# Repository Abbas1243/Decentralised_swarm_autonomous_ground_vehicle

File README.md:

# BE CAPSTONE PROJECT 

## 🤖 Decentralized Swarm Autonomous Ground Vehicles
<p align="left">
  
</p>

---
## 👥 Team Details

| **Sr. No.** | **Name of Student** | **Roll No.** | **Branch** | **Email ID** |
|:---:|:---|:---:|:---|:---|
| 1 | Abbas Najam | 59 |Automation and Robotics | [2023.abbas.najam@ves.ac.in](mailto:2023.abbas.najam@ves.ac.in) |
| 2 | Mayuresh Joshi | 49 | Automation and Robotics | [2023.mayuresh.joshi@ves.ac.in](mailto:2023.mayuresh.joshi@ves.ac.in) |
| 3 | Shravan Umrale | 66 | Automation and Robotics | [2023.shravan.umrale@ves.ac.in](mailto:2023.shravan.umrale@ves.ac.in) |
| 4 | Yash Vaychal | 31 | Automation and Robotics | [2023.yash.vaychal@ves.ac.in](mailto:2023.yash.vaychal@ves.ac.in) |

---

## Guide Details

**Project Guide:**  Deepti Khimani

**Department:** Automation and Robotics  

**Institute:** VESIT, Mumbai

# 📌 Project Overview

Swarm robotics is inspired by the collective behavior observed in nature, such as ants, bees and birds. Many simple units working together can cover more ground, and tolerate the loss of individual units better, than a single capable unit.

This project focuses on the design and development of a **six-robot low-cost differential-drive robotic swarm for cooperative indoor exploration and mapping**.

Each robot is designed around an ESP32-WROOM-32E microcontroller mounted on a custom-designed PCB. The PCB integrates the motor driver and DC-DC buck converter, reducing the need for separate electronic modules and simplifying the overall hardware assembly.

Each robot is equipped with:
- Six VL53L0X Time-of-Flight (ToF) distance sensors.
- One MPU6050 six-axis IMU.
- Two N20 geared DC motors with integrated wheel encoders.
- Two 34 mm rubber drive wheels.
- One ball caster.
- One 7.4 V, 2600 mAh LiPo battery.

The mechanical structure consists of a 3 mm laser-cut MDF base plate, custom 3D-printed PLA motor holders, a caster holder and spacers. M3 nuts and bolts are used for mechanical assembly.

The current implementation assumes that the robots begin from predefined and known starting positions and orientations. Estimating unknown starting poses and automatically aligning independently initialized robot maps are considered future extensions.

### Key Capabilities
Key Capabilities
* 🤖 Low-cost differential-drive robots (ESP32 on custom PCB)
* 📏 6-beam ToF sensing per robot
* 🧭 Odometry from wheel encoders fused with IMU gyro
* 🗺️ Per-robot SLAM using pose graph and scan matching
* 🧩 Merging of all robots' observations into one map
* 📡 Wi-Fi telemetry to a laptop and robot-to-robot pose sharing
* 🚧 Reactive obstacle avoidance and wall following
* 🧠 Decentralized exploration behaviour
* 📊 Live map viewer and replayable data logs
* 📐 Evaluation against tape-measured ground truth
---

# 🎯 Problem Statement

Teams of mobile robots map unknown indoor spaces faster than a single robot, and can keep working if one unit fails. But published multi-robot mapping systems depend on dense 2D LiDAR and a single-board Linux computer on every robot, which puts them out of reach of teaching laboratories and of applications where robots are expendable.

This project therefore designs, builds and evaluates a team of low-cost differential-drive robots, each with only an ESP32, six single-zone ToF sensors, an IMU and wheel encoders, that explore a known-size indoor arena from **known starting poses**, while a laptop combines their data into one two-dimensional map. The problem includes determining, **by measurement and not by assumption**, how accurate such a map is and which sensing, odometry and algorithmic factors limit that accuracy.

---

# 🚀 Objectives

The major objectives of this project are:

* Develop a decentralized multi-robot swarm system.
* Enable communication between multiple autonomous ground vehicles.
* Implement autonomous navigation.
* Implement mapping and localization.
* Develop obstacle avoidance capabilities.
* Implement distributed decision-making.
* Introduce swarm intelligence algorithms.
* Detect communication, sensor, and motor-related faults.
* Develop fault recovery mechanisms.
* Reallocate tasks when a robot becomes unavailable.
* Maintain swarm operation after individual robot failure.
* Validate the system through simulation.
* Develop and test physical AGV prototypes.
* Evaluate swarm performance under different fault conditions.

---
## Existing System

Describe the currently available system or method.

Mention its limitations:

- High cost
- Low accuracy
- Manual process
- Lack of automation
- Poor scalability
- Limited accessibility

---

## Proposed System

### 1. System Overview

The proposed system consists of multiple low-cost ESP32-based mobile robots that independently handle real-time operations such as sensor acquisition, wheel odometry, PID-based motion control, and data transmission. Computationally intensive tasks, including mapping, scan matching, and pose graph optimization, are performed centrally on a laptop.

The system uses a lightweight, open binary communication protocol to exchange sensor and odometry data over Wi-Fi. All transmitted data can also be stored in replayable logs, allowing offline algorithm development, testing, and evaluation.

### 2. System Working Principle

The system operates through the following sequence:

1. **Safe Robot Initialization:** At power-up, all motor driver input pins are configured LOW to prevent unintended motor movement. The ESP32 then connects to the Wi-Fi network and initializes the onboard sensors.

2. **Multi-Sensor Selection:** A custom-milled hub PCB uses a 74HC138 decoder and a 74HC04 inverter to select one of the six VL53L0X time-of-flight distance sensors at a time. Since all six sensors share the same default I2C address, the selection circuit enables individual sensor communication. The main PCB provides only two shutdown control lines.

3. **Odometry and Motion Control:** The robot combines MPU6050 gyroscope measurements with wheel encoder feedback to estimate its movement. Gyroscope bias is calibrated during startup. PID controllers are implemented for wheel speed regulation, angular turning, and linear distance control.

4. **Wireless Data Transmission:** Every 50 ms, each robot transmits a 36-byte binary data frame containing its estimated pose and distance measurements. Each frame includes the robot's own pose at the time of sensor acquisition, eliminating the need for clock synchronization between robots.

5. **Sensor Coverage:** By rotating through a partial angle (ϕ), the robot achieves a theoretical sensor coverage of:

   \[
   \text{Coverage} = 120^\circ + \phi
   \]

   Therefore, a complete 360° coverage requires a 240° rotation.

6. **Centralized Mapping and Optimization:** The laptop receives the transmitted frames and converts sensor measurements into world-coordinate points using a conical sensor model. It then performs scan matching, pose graph optimization, and map merging for robots with known initial positions. The resulting map and robot trajectories are visualized using RViz2.

### 3. Expected Outcomes and Benefits

The proposed system aims to provide the following benefits:

- **Low-Cost Hardware:** A cost-effective and replicable multi-robot platform built around ESP32 microcontrollers.
- **Modular Architecture:** Independent robot-level sensing, communication, odometry, and motion-control operations.
- **Closed-Loop Motion Control:** Calibrated PID-based control for accurate wheel speed, turning, and distance movement.
- **Sparse-Sensor Mapping:** An approach to mapping using six VL53L0X distance sensors, with clearly documented sensing limitations.
- **Offline Development:** Replayable sensor and odometry logs for testing and improving mapping algorithms without requiring physical robot operation.
- **System Validation:** A requirement-to-test structure that tracks implementation and verification status, ensuring that untested requirements remain clearly identified.

### 4. Centralized vs. Decentralized Architecture

The proposed system uses a **centralized mapping architecture with independent robot-level control**.

- **Robot-Level Operations:** Each robot independently handles its motor control, sensor acquisition, odometry estimation, and wireless data transmission. Robots do not require communication with neighbouring robots to perform these operations.
- **Centralized Operations:** Mapping, scan matching, pose graph optimization, and map merging are performed on a central laptop.
- **Optimization Architecture:** The closest published system also performs optimization on a single elected robot. Therefore, the proposed system does not claim to implement fully decentralized SLAM.

This distinction is important because independent robot operation does not necessarily imply decentralized mapping or SLAM.

---

## System Architecture

The proposed system follows a distributed architecture consisting of two main subsystems: an **ESP32-based Automated Guided Vehicle (AGV)** and a **Laptop-based ROS 2 processing system**. Both subsystems communicate wirelessly through Wi-Fi using UDP protocol for real-time data transmission and control.

### 1. AGV – Sensing and Control

The AGV is equipped with six VL53L0X Time-of-Flight (ToF) distance sensors, an MPU6050 IMU, and wheel encoders for environmental sensing and motion estimation.

The ESP32, mounted on a custom PCB, processes sensor data, performs odometry calculations and PID-based motor control, and generates heading-stamped sensor frames. A DRV8833 motor driver controls two N20 motors configured in a differential-drive arrangement.

### 2. Wireless Communication

The AGV communicates with the laptop over Wi-Fi using UDP.

- **Data Transmission:** The ESP32 sends 36-byte sensor data frames at 20 Hz to the laptop.
- **Command Transmission:** The laptop sends 10-byte control commands (Drive/Stop) back to the ESP32.

### 3. Laptop – ROS 2 Processing

The laptop runs Ubuntu with ROS 2 Humble.

- A UDP receiver collects incoming sensor data and logs it into CSV files.
- The ROS 2 bridge processes and publishes odometry, sensor ranges, TF transforms, point clouds, and velocity commands.
- The processed information is passed to the mapping pipeline for further computation.

### 4. Mapping and Visualization

The mapping pipeline consists of a scan builder, cone sensor model, and mapper.

- **Scan Builder:** Converts incoming sensor measurements into scan data.
- **Cone Sensor Model:** Models the sensor's field of view and measurements.
- **Mapper:** Uses scan matching and pose graph techniques to build and optimize the environment map.
- **Map Merger:** Combines mapping results for visualization.
- **RViz2:** Displays the generated map and relevant robot data.

### 5. Overall System Workflow

The complete architecture follows the workflow:

**Sensing → Processing → Wireless Communication → Mapping → Visualization**

This modular architecture integrates embedded systems, real-time motor control, wireless communication, and ROS 2-based mapping to develop an AGV capable of sensing its surroundings and building an environment map.

### Key Features

- Real-time environmental sensing using ToF sensors.
- ESP32-based onboard processing and PID motor control.
- Wireless communication using UDP over Wi-Fi.
- ROS 2-based sensor data processing.
- Scan matching and pose graph-based mapping.
- Real-time map visualization using RViz2.

---

## Hardware Requirements

| Sr. No. | Component | Specification / Model | Quantity |
|:---:|---|---|:---:|
| 1 | Microcontroller | ESP32-WROOM-32E | 6 |
| 2 | Custom PCB | ESP32, motor driver and buck converter integration | 6 |
| 3 | Motor Driver | Integrated on custom PCB | 6 |
| 4 | DC-DC Buck Converter | Integrated on custom PCB | 6 |
| 5 | IMU | MPU6050 (6-axis) | 6 |
| 6 | ToF Sensors | VL53L0X, 6 sensors per robot | 36 |
| 7 | N20 Motors | Geared DC motors with integrated encoders | 12 |
| 8 | Wheel Encoders | Integrated with N20 motors | 12 |
| 9 | Battery | LiPo 7.4 V, 2600 mAh (2S) | 6 |

##  Mechanical Components

| Sr. No. | Component | Specification | Quantity |
|:---:|---|---|:---:|
| 1 | Base Plate | 3 mm MDF, laser cut | 6 |
| 2 | Drive Wheels | 34 mm Mini Car N20 Motor Wheel, rubber | 12 |
| 3 | Caster Wheel | Mini 3Pi Car N20 Caster Robot Ball Wheel | 6 |
| 4 | Motor Holders | PLA 3D printed | 6 sets |
| 5 | Caster Holders | PLA 3D printed | 6 sets |
| 6 | Spacers | PLA 3D printed | 6 sets |
| 7 | Fasteners | M3 nut-and-bolt assembly | As required |

##  Mechanical and Sensor Component Specifications

| Sr. No. | Component | Model / Specification | Quantity | Product Link |
|:---:|---|---|:---:|---|
| 1 | N20 DC Gear Motor | 3V, 150 RPM, with integrated encoder | 12 | [Robu.in](https://robu.in/product/n20-3v-150rpm-micro-metal-gear-motor-with-encoder/) |
| 2 | ToF Distance Sensor | VL53L0X, I2C interface | 36 | [Robu.in](https://robu.in/product/vl53l0x-tof-based-lidar-laser-distance-sensor/) |
| 3 | Drive Wheel | 34 mm Mini Car N20 Motor Wheel, Rubber | 12 | [Robu.in](https://robu.in/product/34mm-mini-car-n20-motor-wheel-rubber-small-wheel/) |
| 4 | Caster Wheel | Mini 3Pi Car N20 Caster Robot Ball Wheel | 6 | [Robu.in](https://robu.in/product/mini-3pi-car-n20-caster-robot-ball-wheel/) |
---

## Software Requirements

The following software and development tools are required to run and develop the project.

| Software / Tool | Purpose |
|---|---|
| Ubuntu | Operating system for ROS 2 processing |
| ROS 2 Humble | Robot communication and data processing |
| Python 3 | UDP receiver, data logging and mapping modules |
| Arduino IDE | ESP32 firmware development and uploading |
| RViz2 | Real-time sensor data and point cloud visualization |
| NumPy | Numerical computations and data processing |
| Matplotlib | Data visualization and plotting |
| teleop_twist_keyboard | Keyboard-based AGV movement control |

### Required Libraries

**ESP32 Firmware Libraries**
- `Adafruit_VL53L0X` – Interface with VL53L0X ToF sensors.
- `Wire` – I2C communication with sensors and peripherals.
- `WiFi` – Wireless network connectivity.
- `WiFiUdp` – UDP-based wireless data transmission.

**Python Libraries**
- `numpy`
- `matplotlib`

### Additional Requirements
- ESP32 Dev Module board support package.
- 2.4 GHz Wi-Fi network for communication between AGV and laptop.
- USB connection for ESP32 programming and serial monitoring (115200 baud).
---

## Technologies Used

The project combines embedded systems, wireless communication, robotics middleware and mapping algorithms.

| Technology | Application |
|---|---|
| ESP32 | Main microcontroller for AGV control and sensing |
| Arduino Framework | Embedded firmware development |
| ROS 2 Humble | Robot middleware and communication |
| Python 3 | Data reception, logging and mapping pipeline |
| UDP Protocol | Real-time wireless sensor data transmission |
| Wi-Fi (2.4 GHz) | Communication between AGV and laptop |
| I2C Protocol | Communication with ToF sensors and IMU |
| PID Control | Closed-loop motor speed, distance and angle control |
| Odometry | Estimation of robot position and orientation |
| SLAM | Simultaneous localization and mapping |
| Scan Matching | Alignment of sensor scans |
| Pose Graph Optimization | Optimization of robot poses |
| RViz2 | Visualization of sensor data and mapping results |

### Mapping and Processing Techniques
- Cone-based sensor modelling.
- Partial-angle scan generation.
- Scan-to-map matching.
- Pose graph-based optimization.
- Multi-robot map merging with known starting poses.

---

## Methodology

The project follows a systematic development and implementation methodology to design and develop a low-cost swarm of ESP32-based differential-drive Automated Guided Vehicles (AGVs) for cooperative 2D indoor mapping. The methodology consists of the following stages:

### 1. Literature Survey

A detailed literature survey was conducted to understand existing approaches and identify suitable techniques for low-cost robotic mapping.

- Study of 2D LiDAR-based SLAM techniques.
- Review of scan matching algorithms such as ICP and Correlative Scan Matching.
- Study of collaborative SLAM and swarm robotics.
- Review of pose graph optimization techniques.
- Exploration of low-cost and sparse range-sensing approaches using Time-of-Flight (ToF) sensors.
- Study of existing frameworks such as Hector SLAM, Cartographer, slam_toolbox and tinySLAM.

### 2. Problem Identification

Existing multi-robot SLAM systems generally require expensive LiDAR sensors and powerful onboard computing platforms.

- The initial Raspberry Pi 4-based architecture was found to be expensive.
- The Milk-V Duo S architecture with RPLIDAR A1 faced computational limitations, with Python feature SLAM exceeding the 100 ms per-scan processing budget.
- Therefore, a low-cost ESP32-based architecture was selected to reduce hardware cost while retaining essential sensing, motion control and wireless communication capabilities.

### 3. Requirement Analysis

Thirteen functional requirements (R1–R13) were defined with measurable acceptance criteria before testing.

The requirements cover:

- Hardware development and sensor integration.
- Wireless communication and data transmission.
- Safe motor operation and command-loss handling.
- Robot geometry calibration and odometry.
- ToF sensor accuracy and scan generation.
- PID-based motion control.
- ROS 2 integration and live visualization.
- Scan matching and pose graph optimization.
- Multi-robot map merging.
- Data logging and system cost.

Each requirement was linked to its corresponding design element and validation test.

### 4. System Design

The final architecture was divided into two major subsystems:

**AGV Subsystem:**
- ESP32-WROOM-32E microcontroller on a custom PCB.
- Six VL53L0X ToF sensors arranged in a 120° front-facing arc.
- MPU6050 IMU and wheel encoders.
- Hub PCB using a 74HC138 decoder and 74HC04 inverter for sequential sensor selection.
- DRV8833 motor drivers and two N20 geared motors in a differential-drive configuration.

**Laptop Subsystem:**
- Ubuntu operating system with ROS 2 Humble.
- Python-based UDP receiver and CSV logger.
- ROS 2 communication bridge.
- Scan builder and cone-based sensor model.
- Scan matching and pose graph optimization.
- Map merging and RViz2 visualization.

A binary UDP communication protocol was designed for wireless data exchange between the AGVs and laptop.

### 5. Hardware and Software Development

The hardware and software components were developed and implemented separately before integration.

**Hardware Development:**
- Design and fabrication of the custom ESP32 PCB.
- Development of the sensor hub PCB.
- 3D printing of the ToF sensor mounting arc and mechanical holders.
- Assembly of the chassis, motors, wheels and power supply.
- Integration of the IMU, encoders and six ToF sensors.

**Software Development:**
- ESP32 firmware for sensor acquisition, odometry and PID motor control.
- Python-based UDP receiver and CSV data logger.
- ROS 2 bridge for publishing odometry, sensor ranges, transforms and point clouds.
- Python-based scan builder, sensor model, scan matcher and pose graph modules.
- Development of a tinySLAM-style onboard scan-to-map matcher for synthetic testing.

### 6. System Integration

The system was integrated incrementally to identify and resolve hardware and software issues at each stage.

The integration sequence followed:

1. ESP32 firmware flashing and serial monitoring.
2. Standalone UDP receiver testing.
3. ROS 2 bridge integration.
4. Sensor data visualization in RViz2.
5. Keyboard-based AGV movement control.
6. Hub PCB integration and sequential sensor initialization.
7. Integration of all six ToF sensors and the MPU6050.
8. Odometry calibration and PID controller tuning.
9. Complete wireless communication and system testing.

Each subsystem was checked before proceeding to the next integration stage.

### 7. Mapping Methodology

The mapping approach is based on a sparse pose-graph SLAM method adapted from the literature, particularly the approach described by Friess et al. The algorithm was independently reimplemented; the authors' GPL-3.0 source code was neither inspected nor copied.

**Step 1 – Point Generation**
- Convert each ToF measurement into a spatial point using the robot pose, sensor mounting angle and measured distance.
- Use the heading estimate recorded at the time of measurement.
- Combine the readings collected during a spin into a scan.

**Step 2 – Pose Graph Construction**
- Create one pose node for each robot waypoint.
- Connect consecutive nodes using odometry constraints.
- Store relative motion information between successive poses.

**Step 3 – Scan Matching**
- Match scans between nearby robot poses to estimate relative transformations.
- Use Correlative Scan Matching to search for the best alignment over position (x, y) and orientation (θ).
- Apply ICP refinement to improve the estimated alignment.
- Add the resulting scan-matching constraints to the pose graph.

**Step 4 – Pose Graph Optimization**
- Apply Gauss–Newton optimization to minimize the error between measured and predicted relative poses.
- Refine the estimated robot trajectory using odometry and scan-matching constraints.

**Step 5 – Map Generation**
- Re-project sensor scans using the optimized robot poses.
- Combine the corrected points to generate the environment map.
- Convert the resulting map into an occupancy grid for visualization.

**Additional Improvements for Sparse ToF Sensing:**
- Range-dependent cone-based sensor uncertainty modelling.
- Treat invalid or no-return sensor readings as unknown.
- Apply a short temporal median filter to reduce measurement noise.
- Use Correlative Scan Matching before ICP refinement to improve alignment with sparse sensor data.

### 8. Testing and Validation

A structured validation plan consisting of twelve tests (T1–T12) was defined to evaluate the system against the thirteen requirements.

Testing was conducted in different environments depending on the requirement:

- **Bench Testing:** Sensor initialization, hardware operation, calibration and motor safety.
- **Arena Testing:** Robot movement, turning accuracy, sensor measurements and wireless communication.
- **Replay Testing:** Processing recorded sensor logs on the laptop.
- **Simulation Testing:** Evaluation of mapping algorithms using synthetic data.

The validation process included:

- Sensor range accuracy and measurement noise.
- UDP transmission rate and packet loss.
- Command-loss safety and motor stopping response.
- Wheel odometry and PID motion accuracy.
- Sensor scan generation and RViz2 visualization.
- Scan matching and mapping performance.
- Multi-robot map merging.

### 9. Documentation and Publication

- Document the hardware design, software implementation and system architecture.
- Maintain source code, configuration files and reproducible test logs.
- Record the results, limitations and future improvements.
- Prepare the final BE project report and research paper.
- Publish the project documentation and implementation details on GitHub.

---

### Key Design Calculations

The following calculations were considered during system design and sensor modelling:

**1. Heading Error**

The lateral displacement caused by heading error is approximately:

\[
\epsilon_\perp \approx d\Delta\psi
\]

A heading error of 1° produces approximately 1.7 cm of lateral displacement for a point 1 m away.

**2. Sensor Cone Uncertainty**

The approximate lateral uncertainty is:

\[
\sigma_\perp \approx d\tan(\beta)
\]

For a 25° sensor cone, the uncertainty is approximately 0.44 m at a distance of 1 m, contributing to thick walls and reduced map accuracy.

**3. Sensor Sweep Time**

Since the six ToF sensors are read sequentially:

\[
T_{sweep}=N(t_b+t_{sel})
\]

Where:
- \(N\) = Number of sensors (6).
- \(t_b\) = Sensor ranging time.
- \(t_{sel}\) = Sensor selection, wake-up and configuration time.

With a 33 ms timing budget and assuming zero selection overhead, the calculated lower bound is approximately 200 ms. The actual selection time has not yet been measured on the robot.

**4. Spin Scan Coverage**

The total angular coverage is:

\[
\Theta=120^\circ+\phi
\]

Where \(\phi\) is the robot's spin angle. Full 360° coverage requires a 240° spin, taking approximately 5.3 seconds at 45°/s.

---

### Risk Management

| Risk ID | Identified Risk | Mitigation Strategy |
|---|---|---|
| K1 | Project schedule constraints | Prioritize motion control, scanning and mapping; freeze features when required. |
| K2 | Sparse or noisy ToF measurements | Perform sensor characterization and consider multizone sensors. |
| K3 | Heading drift affecting scan accuracy | Calibrate gyro bias, use closed-loop turns and stop-and-scan operation. |
| K4 | Incorrect scan matching in symmetric environments | Use asymmetric obstacles, residual checks and known starting positions. |
| K5 | Difficulty explaining implementation and contributions | Maintain contribution records, disclose AI assistance and conduct code walkthroughs. |

---

### Overall Methodology Workflow

**Literature Survey → Problem Identification → Requirement Analysis → System Design → Hardware & Software Development → System Integration → Mapping & Optimization → Testing & Validation → Documentation & Publication**

**Expected Outcome:** A low-cost, modular and scalable ESP32-based AGV platform designed for cooperative 2D indoor mapping using sparse ToF sensing, wireless communication and ROS 2-based processing.
---

## Project Timeline

| Week | Task Planned | Status |
|:---:|---|:---:|
| Week 1 | Problem finalization (final architecture fixed after Phase 1 and Phase 2) | Completed |
| Week 2 | Literature survey | Completed |
| Week 3 | Requirement analysis (R1 to R13, T1 to T12) | Completed |
| Week 4 | System design (Main PCB, Hub PCB, arc, and communication protocol) | Completed |
| Week 5 | Prototype development (Robot assembly; 4 out of 6 robots operational) | In Progress |
| Week 6 | Testing and validation (T1 to T12) | completed |
| Week 7 | Project documentation | completed  |
| Week 8 | Research paper writing | completed |

---

## 📅 Weekly Progress Updates

| Week | Date | Work Completed | Work Planned for Next Week | Issues / Challenges | GitHub Commit Link |
|---|---|---|---|---|---|
| **Week 1** | 08 February 2026 | Conducted literature survey on 2D SLAM, scan matching, collaborative SLAM and low-cost range sensing. Identified project objectives and limitations of existing hardware platforms. | Finalize project architecture and identify hardware and software requirements. | High computational requirements and cost of Raspberry Pi-based architecture; Milk-V Duo S performance limitations. | — |
| **Week 2** | 15 March 2026 | Finalized ESP32-based AGV architecture. Studied sensor configurations, differential-drive mechanism and wireless communication requirements. | Prepare requirement specifications, acceptance criteria and project test plan. | Selecting suitable low-cost sensors and balancing sensing accuracy with hardware cost. | — |
| **Week 3** | 12 April 2026 | Defined 13 functional requirements (R1–R13) and 12 validation tests (T1–T12). Finalized system design, sensor arrangement and UDP communication protocol. | Design custom ESP32 PCB, sensor hub PCB and mechanical mounting structure. | Sequential addressing of six VL53L0X sensors and I2C communication constraints. | — |
| **Week 4** | 24 May 2026 | Developed the custom ESP32 PCB and hub PCB using 74HC138 decoder and 74HC04 inverter. Designed the six-sensor mounting arc and AGV mechanical structure. | Assemble AGV hardware and develop ESP32 firmware for sensor acquisition and motor control. | PCB integration, sensor selection and mechanical alignment. | — |
| **Week 5** | 28 June 2026 | Integrated ESP32, six VL53L0X sensors, MPU6050, wheel encoders and N20 motors. Developed firmware for odometry, PID control and UDP communication. Implemented Python UDP receiver and CSV logger. | Integrate the ROS 2 bridge and test live sensor visualization and keyboard-based movement control. | Sensor initialization, Wi-Fi communication jitter and motor direction calibration. | — |
| **Week 6** | 09 August 2026 | Integrated the AGV with Ubuntu and ROS 2 Humble. Implemented ROS 2 topics, odometry publishing and RViz2 visualization. Performed sensor calibration and PID tuning. | Evaluate scan generation, develop the cone sensor model and begin mapping algorithm implementation. | Heading drift, sparse sensor measurements and scan alignment accuracy. | — |
| **Week 7** | 27 September 2026 | Developed Python-based scan builder, cone sensor model, scan matching and pose graph optimization modules. Evaluated the tinySLAM-style matcher using synthetic data. | Analyze simulation results, review system limitations and prepare project documentation and research paper. | Sparse ToF measurements, cone uncertainty and lack of real-robot mapping validation. | — |
| **Week 8** | 01 November 2026 | Consolidated experimental results, analyzed performance against acceptance criteria and documented hardware, software, system architecture, methodology and limitations. Prepared final BE report and research paper. | Finalize GitHub repository, presentation and future development plan. | Real-data mapping and multi-robot map merging remain unvalidated. | — |

---

## Design Files

Upload and link all design files here.

| File Type       | File Name / Link | Description |
| --------------- | ---------------- | ----------- |
| CAD Model       |                  |             |
| Circuit Diagram |                  |             |
| PCB Design      |                  |             |
| Flowchart       |                  |             |
| Simulation File |                  |             |

---

## Circuit Diagram

Add circuit diagram image here.

```markdown

```

---

## Flowchart / Algorithm

### Algorithm

## 🔄 Flowchart & Algorithm

The system operates through two interconnected algorithms: **Robot Firmware (ESP32)** and the **Laptop Processing Pipeline (ROS 2)**. The robot continuously collects sensor data, estimates its position, controls its motors and transmits information wirelessly. The laptop receives the data, processes sensor information, performs mapping and visualizes the results.

### 1. General Flowchart

The overall system follows these steps:

1. **Start:** Begin system execution.
2. **Initialize System:** Initialize the hardware, sensors, communication interfaces and software modules.
3. **Read Input:** Acquire data from sensors or user commands.
4. **Process Data:** Process sensor readings, calculate robot position and interpret incoming commands.
5. **Generate Output / Control Action:** Generate motor-control signals or mapping results.
6. **Display / Store / Transmit Result:** Display the results, store sensor data and transmit information between the AGV and laptop.
7. **Stop:** Stop system execution or safely terminate operation.

### 2. Robot Firmware Algorithm (ESP32)

The ESP32 firmware manages sensor acquisition, robot localization, motor control and wireless communication.

1. **Motor Safety Initialization:** Set all motor-driver inputs LOW to ensure the motors remain stopped during startup.
2. **System Initialization:** Connect to Wi-Fi with Wi-Fi sleep disabled and initialize the six VL53L0X ToF sensors and MPU6050 IMU.
3. **Gyroscope Calibration:** Calibrate the gyroscope bias during startup.
4. **Sensor Acquisition:** Select each ToF sensor through the hub PCB, read its distance measurement and move to the next sensor.
5. **Odometry Calculation:** Decode both wheel encoders and integrate gyroscope measurements to estimate the robot pose \((x, y, \theta)\).
6. **PID Motor Control:** Execute PID control loops for wheel speed, turning angle and driving distance.
7. **Wireless Data Transmission:** Transmit a 36-byte UDP data frame at 20 Hz. Stop the motors if no command is received within 500 ms.
8. **Continuous Execution:** Repeat the sensing, processing, control and communication cycle.

### 3. Laptop Processing Algorithm (ROS 2)

The laptop processes the received AGV data and performs mapping and visualization.

1. **UDP Data Reception:** Receive and decode incoming UDP frames. Store each frame as a CSV row with its sequence number and calculate packet loss using sequence-number gaps.
2. **ROS 2 Bridge:** Publish robot odometry (`/robot_N/odom`), `ranges_mm`, individual `tof_I/range` topics, `scan_points` and TF transforms. Convert `/robot_N/cmd_vel` commands into wheel-control commands.
3. **Scan Generation:** The scan builder converts sensor measurements into spatial scan points using the cone-based sensor model.
4. **Scan Matching and Optimization:** Match consecutive scans using Correlative Scan Matching followed by ICP refinement. Add constraints to the pose graph and optimize the estimated robot trajectory.
5. **Multi-Robot Mapping:** For multiple robots with known starting positions, add inter-robot constraints when their estimated poses are sufficiently close. Optimize the combined pose graph and render the merged map.

### 4. Overall Algorithm Workflow

**Start → Initialize → Sensor Acquisition → Data Processing → Odometry & PID Control → UDP Communication → ROS 2 Processing → Scan Generation → Scan Matching → Pose Graph Optimization → Map Visualization**

For multiple AGVs, the optimized individual mapping information is combined through inter-robot pose constraints to produce a cooperative map.

### 5. Safety and Communication Handling

- All motor-driver inputs are initialized LOW during startup.
- Wi-Fi sleep is disabled to support communication.
- The ESP32 transmits sensor data at 20 Hz using UDP.
- A 500 ms command timeout stops the motors when communication is interrupted.
- UDP sequence numbers are used to identify missing data frames.

---

## Implementation Details

Explain the actual implementation of the project.

### Hardware Implementation

Write details about connections, components, power supply, sensors, actuators, PCB, enclosure, etc.

### Software Implementation

Write details about code structure, libraries used, algorithms, communication protocols, database, app, cloud, etc.

---

## Code Structure

```text
BE-Capstone-Project/
│
├── README.md
├── docs/
│   ├── literature_survey.md
│   ├── project_report.pdf
│   └── presentation.pptx
│
├── hardware/
│   ├── circuit_diagram.png
│   ├── pcb_design/
│   └── cad_model/
│
├── software/
│   ├── src/
│   ├── include/
│   └── tests/
│
├── images/
│   ├── system_architecture.png
│   ├── prototype_photo.jpg
│   └── results.png
│
└── references/
    └── papers/
```

---

## How to Run the Project

### Step 1: Clone the Repository

```bash
git clone https://github.com/username/project-name.git
```

### Step 2: Install Dependencies

```bash
pip install -r requirements.txt
```

or mention specific software/library installation steps.

### Step 3: Upload / Run the Code

```bash
python main.py
```

or

```bash
arduino-cli upload -p COMx --fqbn board_name
```

### Step 4: Observe the Output

Mention the expected output of the project.

---

## Testing and Results

| Test No. | Test Description | Expected Result | Actual Result | Status      |
| -------- | ---------------- | --------------- | ------------- | ----------- |
| 1        |                  |                 |               | Pass / Fail |
| 2        |                  |                 |               | Pass / Fail |
| 3        |                  |                 |               | Pass / Fail |

---

## Result Images / Videos

Add images or videos of the working prototype.

```markdown

```

Video Link: https://youtu.be/-i1T_cCoHbY

```markdown
[Project Demo Video](https://drive.google.com/your-video-link)
```

---

## Applications

1. Education and Research
   - A cheap platform for students and labs to study multi-robot SLAM and swarm behaviour without expensive sensors.

2. Indoor Mapping of Unknown Spaces
   - Multiple low-cost robots can map rooms or corridors faster than one robot.

3. Search and Rescue (Prototype Level)
   - Many inexpensive, expendable robots can explore collapsed or hazardous indoor areas.

4. Industrial and Warehouse Inspection
   - Small robots can map aisles and detect layout changes, cheaply and in parallel.

5. Hazardous Environment Exploration
   - Low-cost units can be risked in places that are unsafe for people.

6. Platform for Larger Swarm Experiments
   - The design can scale to more robots because each unit is inexpensive.

---

## Advantages

1. **Low-Cost Hardware Architecture**

   Uses ESP32 microcontrollers and integrated custom PCBs instead of expensive onboard computing platforms.

2. **Six-Robot Experimental Platform**

   Allows investigation of multi-robot cooperation rather than limiting experimentation to a single robotic platform.

3. **Custom PCB Integration**

   Integrates the microcontroller, motor driver and buck converter on a common PCB, reducing separate modules and wiring.

4. **Modular Mechanical Design**

   Laser-cut MDF and 3D-printed PLA components make mechanical modifications and replacement easier.

5. **ROS 2 Integration**

   Provides a flexible software environment for developing robot communication, mapping and visualization.

6. **Scalable Experimental Architecture**

   Provides a foundation for studying the addition of further robots, subject to communication, processing and hardware limitations.

7. **Practical Engineering Experience**

   Involves PCB development, embedded programming, mechanical design, 3D printing, ROS 2 and multi-robot system integration.

---

## Limitations

1. Sparse and Short-Range Sensing
   - VL53L0X sensors are single-zone, with about a 25 degree cone and a practical indoor range of about 1.2 m, worse on dark, glossy or sunlit surfaces. Scans are sparse compared with lidar.

2. Centralized Mapping
   - Mapping and optimization run on the laptop, so the system is not fully decentralized and depends on the laptop and Wi-Fi link for the merged map.

3. Accuracy Gain Only Where Paths Overlap
   - Away from overlapping regions each robot drifts like a single robot. Wheel slip and heading drift dominate odometry error.

4. Known Starting Poses
   - The current scope assumes known starting poses. Merging with unknown starting poses is future work.

5. Environment Sensitivity
   - Symmetric rooms and long featureless corridors make scan matching less reliable.

6. Battery and Communication Limits
   - Limited battery life, and Wi-Fi channel sharing between the laptop link and robot-to-robot messages can cause packet loss.

---

## Future Scope 

1. Unknown Starting Poses
   - Align robots' maps without known starts using multi-resolution correlative matching of submaps, with strict acceptance gates (score, overlap, margin, repeated consistency) to prevent wrong merges, and a measured false-merge rate in symmetric arenas.

2. Inter-Robot Relative Observations
   - Use rendezvous or markers to add direct robot-to-robot constraints to the pose graph.

3. Sensor Upgrade
   - Move to multizone ToF sensors (for example VL53L5CX) for denser scans if the VL53L0X array proves too sparse. Cost, size and driver complexity must be checked first.

4. More Decentralized Mapping
   - Move parts of mapping onto the robots, and elect a robot to run optimization, as in the ETH swarm work.

5. Fault Detection and Task Reallocation
   - Carry over ideas from the earlier project: detect communication, sensor and motor faults, and reassign exploration to other robots.

6. Ground-Truth Evaluation
   - Overhead camera with printed markers on the robots for pose error over time, used for evaluation only.

---

## Research Paper / Publication

| Item                      | Details                                                   |
| ------------------------- | --------------------------------------------------------- |
| Paper Title               |                                                           |
| Conference / Journal Name |                                                           |
| Paper Status              | Not Started / Drafting / Submitted / Accepted / Published |
| Submission Date           |                                                           |
| Paper Link                |                                                           |

---

## References

Add references in IEEE format.

Example:

```text
[1] A. Author, B. Author, "Title of the Paper," Journal/Conference Name, vol. X, no. Y, pp. xx-yy, Year.
[2] Datasheet / Website / Book reference.
```

---

## Repository Update Guidelines

Each student team must update the GitHub repository regularly.

Minimum expected updates:

* Update README every week.
* Push code changes regularly.
* Upload circuit diagrams, CAD files, PCB files, reports and presentations.
* Add weekly progress in the progress table.
* Maintain proper folder structure.
* Do not upload unnecessary temporary files.
* Each major update should have a meaningful commit message.

Example commit messages:

```text
Added problem statement and objectives
Updated system architecture diagram
Added sensor interfacing code
Updated weekly progress for Week 3
Added testing results and prototype images
```

---

## Declaration

We declare that this project work is carried out by our team as part of the BE Capstone Project. The work will be regularly updated on GitHub and all references used will be properly cited.

---

## License

This project is for academic use only.

Optional:

```text
MIT License / Creative Commons / Institute Use Only
```

```
```

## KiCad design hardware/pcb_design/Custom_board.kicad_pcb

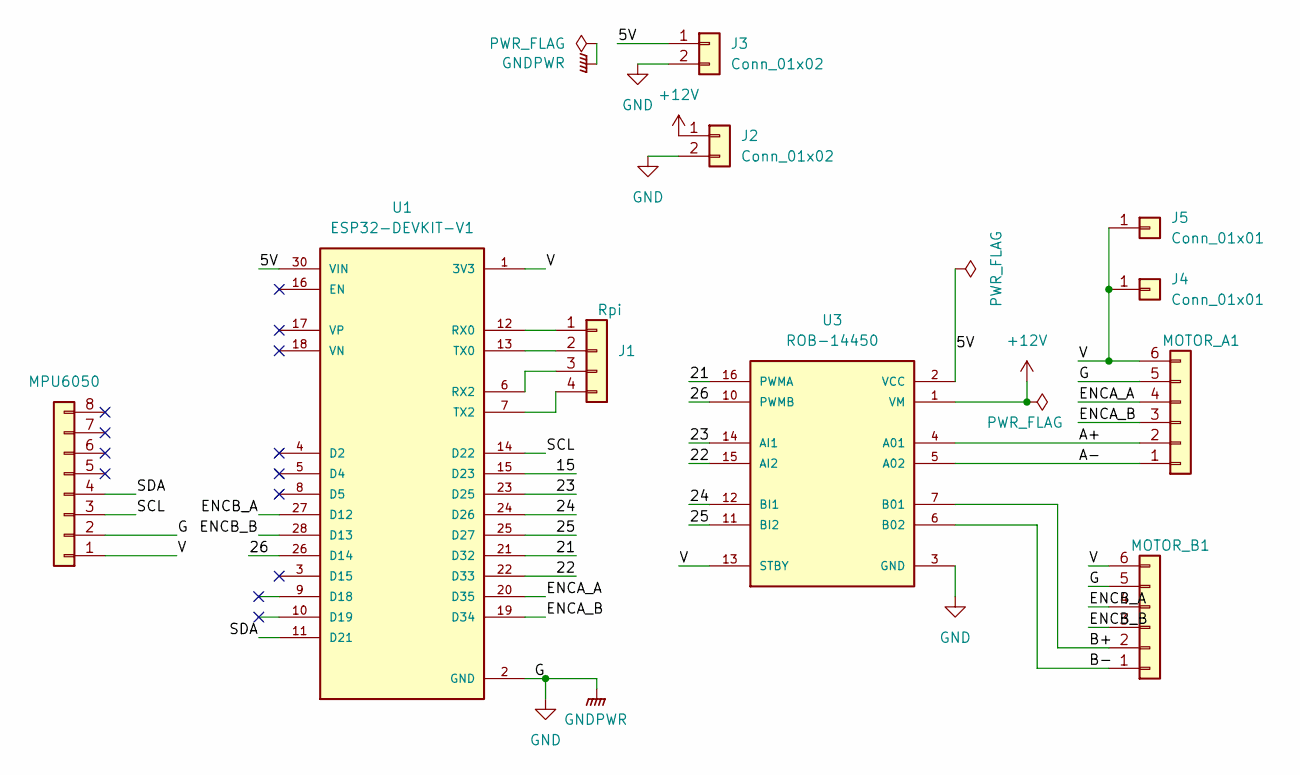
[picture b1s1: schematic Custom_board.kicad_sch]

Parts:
J1: Rpi; PinHeader_1x04_P2.54mm_Vertical
J2, J3: Conn_01x02; PinSocket_1x02_P2.54mm_Vertical
J4, J5: Conn_01x01; PinSocket_1x01_P2.54mm_Vertical
MOTOR_A1: Conn_01x06; PinHeader_1x06_P1.27mm_Vertical
MOTOR_B1: Conn_01x06; PinHeader_1x06_P1.27mm_Vertical
MPU6050: Conn_01x08; PinSocket_1x08_P2.54mm_Vertical
U1: ESP32-DEVKIT-V1; MODULE_ESP32_DEVKIT_V1; PARTREV N/A
U3: ROB-14450; MODULE_ROB-14450; PARTREV 11-13-17

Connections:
+12V: J2.1, U3.1 (VM)
/5V: J3.1, U1.30 (VIN), U3.2 (VCC)
/15: U1.15 (D23)
/21: U1.21 (D32), U3.16 (PWMA)
/22: U1.22 (D33), U3.15 (AI2)
/23: U1.23 (D25), U3.14 (AI1)
/24: U1.24 (D26), U3.12 (BI1)
/25: U1.25 (D27), U3.11 (BI2)
/26: U1.26 (D14), U3.10 (PWMB)
/A+: MOTOR_A1.2, U3.4 (A01)
/A-: MOTOR_A1.1, U3.5 (A02)
/B+: MOTOR_B1.2, U3.7 (B01)
/B-: MOTOR_B1.1, U3.6 (B02)
/ENCA_A: MOTOR_A1.4, U1.20 (D35)
/ENCA_B: MOTOR_A1.3, U1.19 (D34)
/ENCB_A: MOTOR_B1.4, U1.27 (D12)
/ENCB_B: MOTOR_B1.3, U1.28 (D13)
/SCL: MPU6050.3, U1.14 (D22)
/SDA: MPU6050.4, U1.11 (D21)
/V: J4.1 (Pin_1_1), J5.1 (Pin_1_1), MOTOR_A1.6, MOTOR_B1.6, MPU6050.1, U1.1 (3V3), U3.13 (STBY)
GND: J2.2, J3.2, MOTOR_A1.5, MOTOR_B1.5, MPU6050.2, U1.2 (GND), U1.29 (GND), U3.3 (GND), U3.8 (GND), U3.9 (GND)
unnamed: J1.1, U1.12 (RX0)
unnamed: J1.2, U1.13 (TX0)
unnamed: J1.3, U1.6 (RX2)
unnamed: J1.4, U1.7 (TX2)

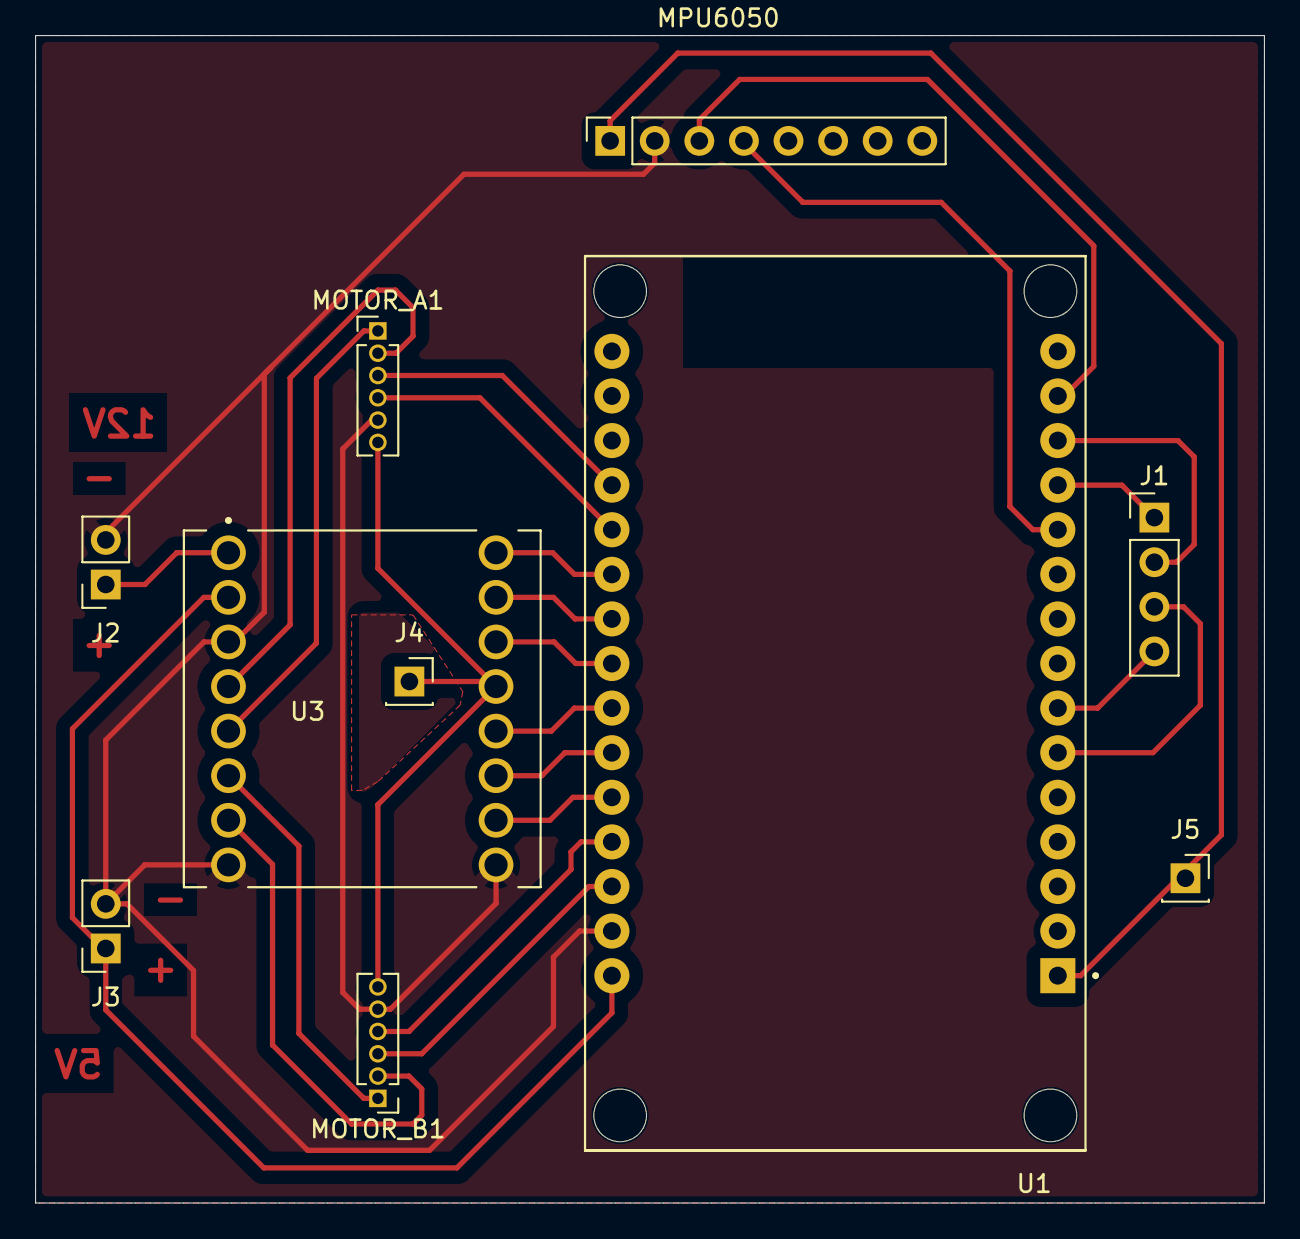
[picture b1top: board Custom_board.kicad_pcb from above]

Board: 2 copper layers, 70.0 x 66.5 mm, 10 parts (0 on the bottom side), 24 nets.
